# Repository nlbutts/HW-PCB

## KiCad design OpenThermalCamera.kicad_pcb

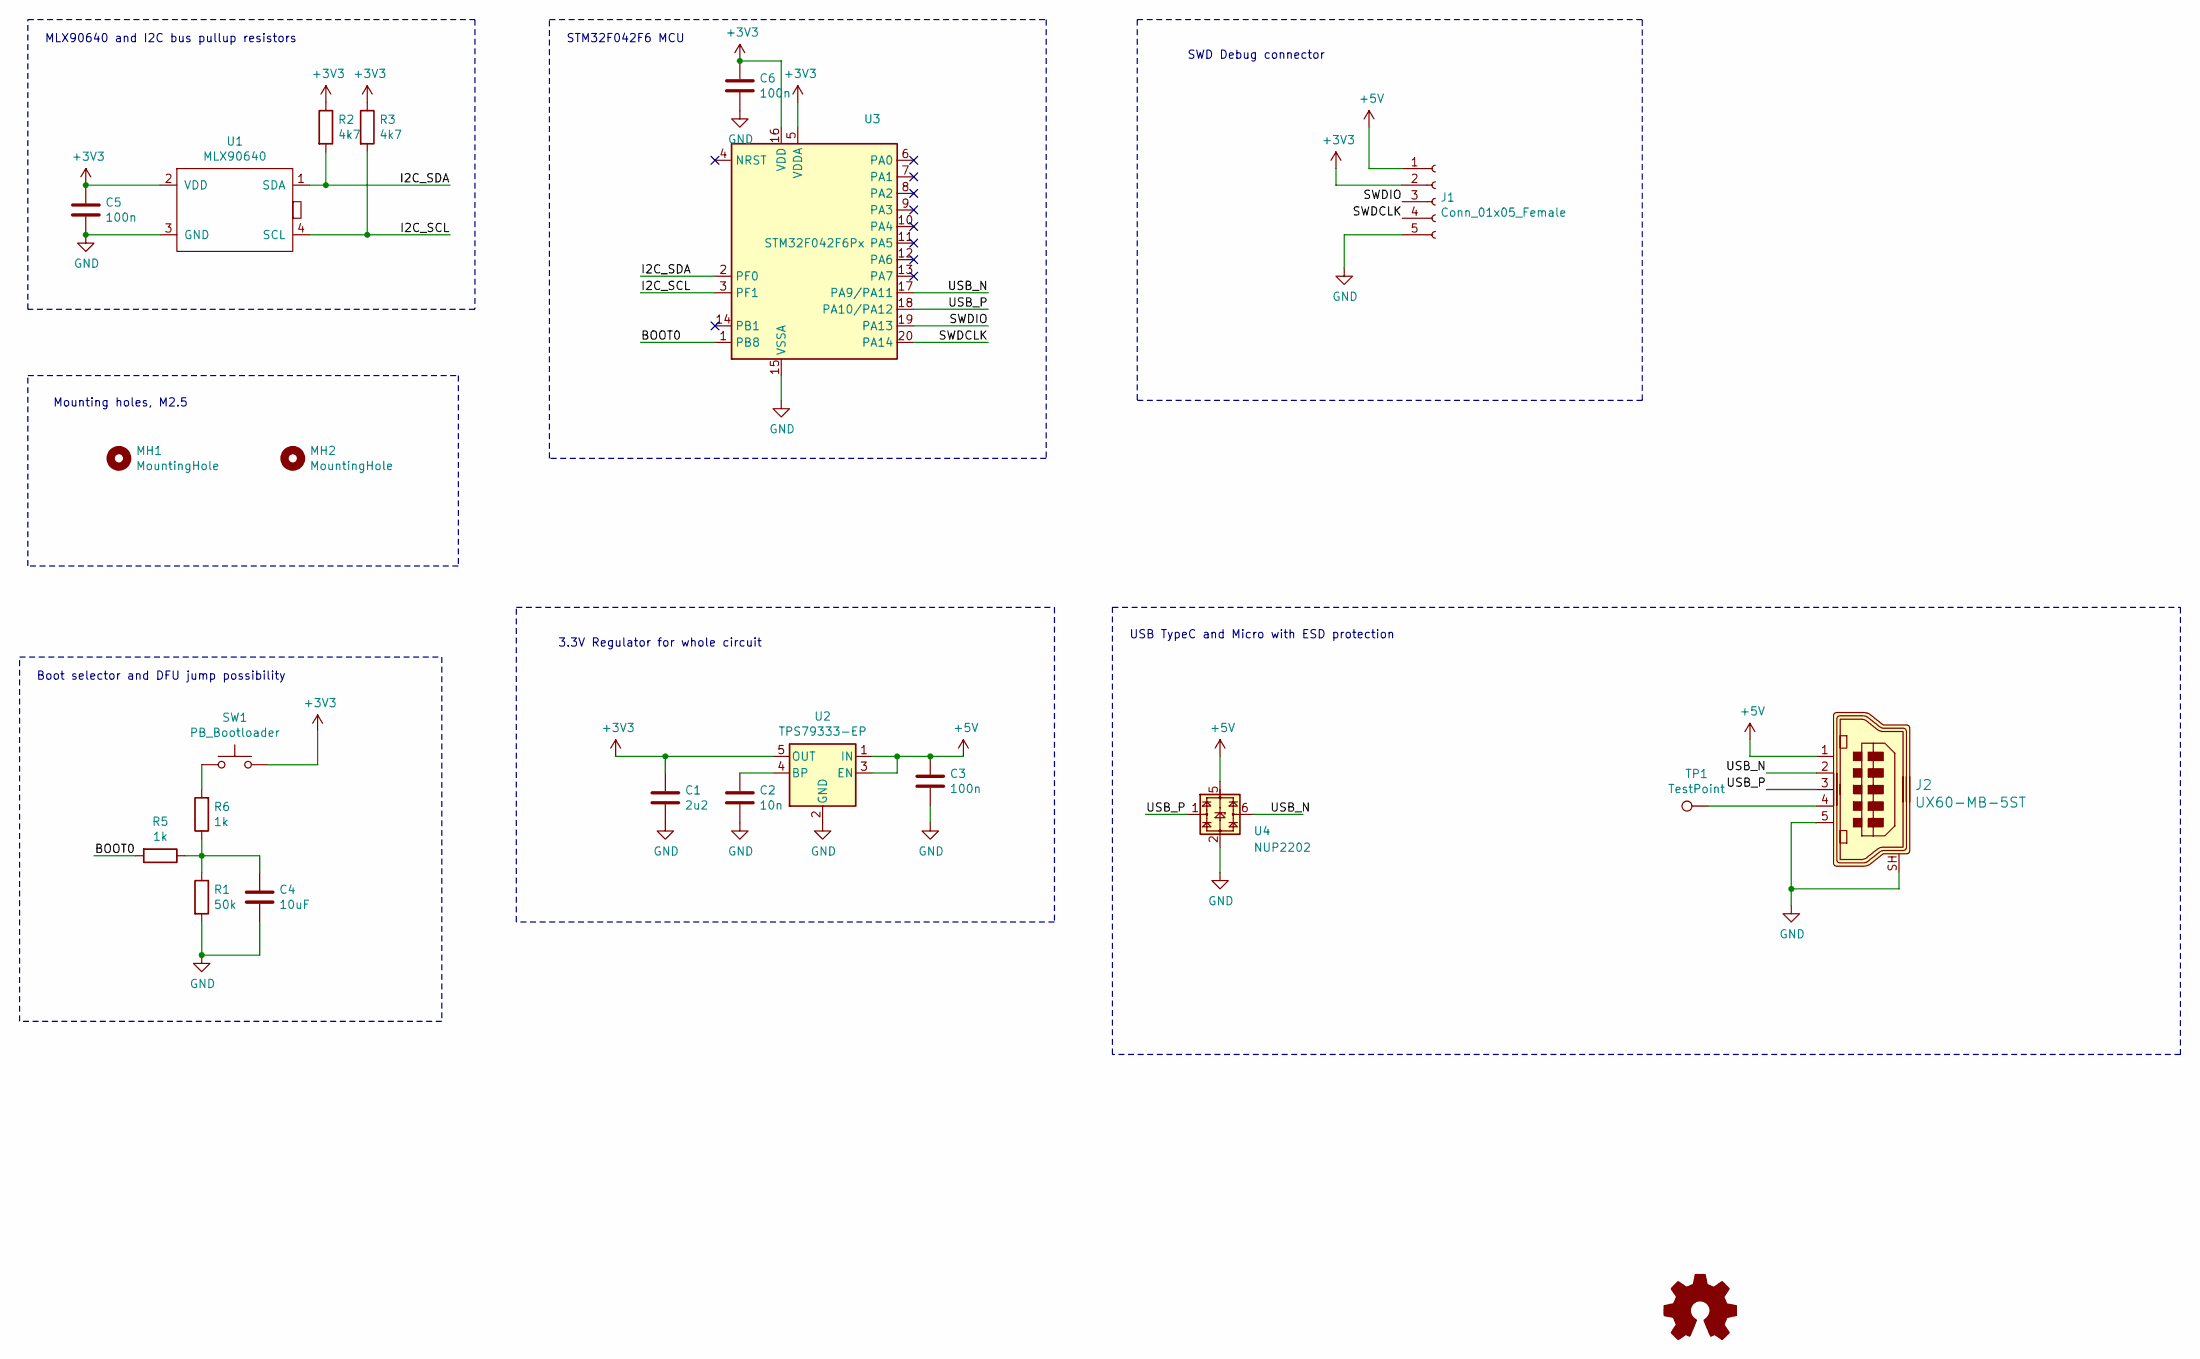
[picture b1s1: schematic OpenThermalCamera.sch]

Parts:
C1: 2u2; C_0805_2012Metric_Pad1.15x1.40mm_HandSolder; Part Number 2896530
C2: 10n; C_0805_2012Metric_Pad1.15x1.40mm_HandSolder; Part Number 2534050
C3, C6: 100n; C_0805_2012Metric_Pad1.15x1.40mm_HandSolder; Part Number 2496943
C4: 10uF; C_0805_2012Metric_Pad1.15x1.40mm_HandSolder; mfr# C2012X5R1C106K085AC
C5: 100n; C_0805_2012Metric_Pad1.15x1.40mm_HandSolder; mfr# 0805B104K250CT
G1: Logo_Open_Hardware_Small; OSHW-Logo2_7.3x6mm_SilkScreen
J1: Conn_01x05_Female; PinHeader_1x05_P1.27mm_Vertical
J2: UX60-MB-5ST; USB_Mini_B_Female_UX60-MB-5ST; MPN UX60-MB-5ST; Digi-Key_PN H2959CT-ND
MH1, MH2: MountingHole; MountingHole_2.7mm_M2.5
R1: 50k; R_0805_2012Metric_Pad1.15x1.40mm_HandSolder; mfr# CRCW080551K0JNEA
R2, R3: 4k7; R_0805_2012Metric_Pad1.15x1.40mm_HandSolder; mfr# CRCW08054K70FKEA
R5, R6: 1k; R_0805_2012Metric_Pad1.15x1.40mm_HandSolder; mfr# CRCW08051K00FKEAC
SW1: PB_Bootloader; SolderJumper-2_P1.3mm_Open_RoundedPad1.0x1.5mm; Part Number /
TP1: TestPoint; TestPoint_Pad_D1.0mm
U1: MLX90640; Part Number 482-MLX90640ESFBABSP
U2: TPS79333-EP; SOT-23-5; mfr# TPS79333DBVR
U3: STM32F042F6Px; TSSOP-20_4.4x6.5mm_P0.65mm; Part Number 511-STM32F042F6P6TR
U4: NUP2202; SOT-363_SC-70-6; Part Number 2533276

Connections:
+3V3: C1.1, C5.1, C6.1, J1.2, R2.1, R3.1, SW1.2, U1.2 (VDD), U2.5 (OUT), U3.5 (VDDA), U3.16 (VDD)
+5V: C3.1, J1.1, J2.1, U2.1 (IN), U2.3 (EN), U4.5
/BOOT0: R5.2, U3.1 (PB8)
/I2C_SCL: R3.2, U1.4 (SCL), U3.3 (PF1)
/I2C_SDA: R2.2, U1.1 (SDA), U3.2 (PF0)
/SWDCLK: J1.4, U3.20 (PA14)
/SWDIO: J1.3, U3.19 (PA13)
/USB_N: J2.2, U3.17 (PA9/PA11), U4.6
/USB_P: J2.3, U3.18 (PA10/PA12), U4.1
GND: C1.2, C2.2, C3.2, C4.2, C5.2, C6.2, J1.5, J2.5, J2.SH, R1.2, U1.3 (GND), U2.2 (GND), U3.15 (VSSA), U4.2
unnamed: C2.1, U2.4 (BP)
unnamed: C4.1, R1.1, R5.1, R6.1
unnamed 12: J2.4, TP1.1; also elsewhere on the board
unnamed: R6.2, SW1.1

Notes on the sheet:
SWD Debug connector
USB TypeC and Micro with ESD protection
3.3V Regulator for whole circuit
MLX90640 and I2C bus pullup resistors
STM32F042F6 MCU
Boot selector and DFU jump possibility
Mounting holes, M2.5

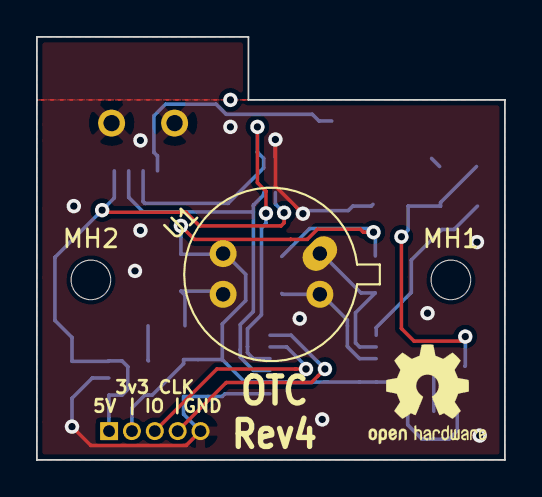
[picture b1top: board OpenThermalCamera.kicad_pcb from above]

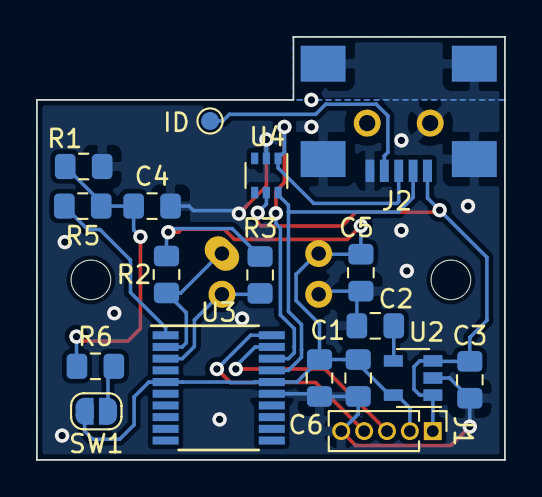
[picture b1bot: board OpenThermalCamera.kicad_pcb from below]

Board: 2 copper layers, 26.0 x 23.5 mm, 22 parts (18 on the bottom side), 14 nets.

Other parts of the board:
ID: TestPoint; TestPoint_Pad_D1.0mm

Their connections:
unnamed 12: ID.1; also elsewhere on the board

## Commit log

2020-01-12 Order the board.
